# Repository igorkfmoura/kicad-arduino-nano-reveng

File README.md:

# Arduino Nano CH340G Reverse Engineering

## Description

Made on KiCad using manual measurements without consulting official schematics for study purposes.

You may find the pdf version of the  in *./extra* folder.

## Other sources of good knowledge

http://actrl.cz/blog/index.php/2016/arduino-nano-ch340-schematics-and-details/

https://www.instructables.com/id/Arduino-Nano-ATmega238PCH340G-v30-PCB-layout/

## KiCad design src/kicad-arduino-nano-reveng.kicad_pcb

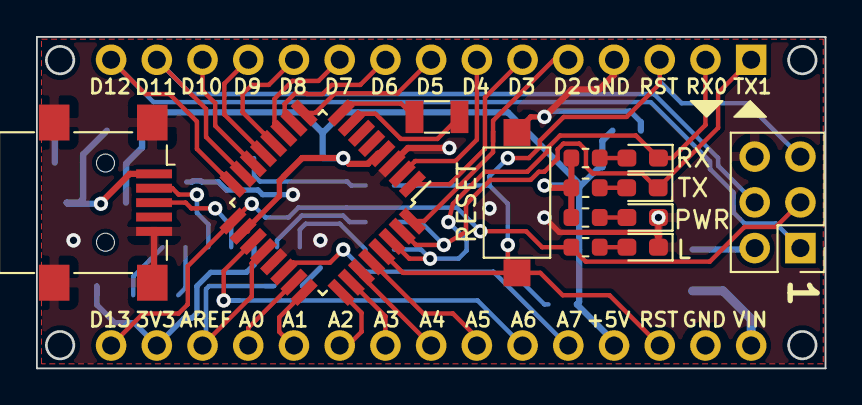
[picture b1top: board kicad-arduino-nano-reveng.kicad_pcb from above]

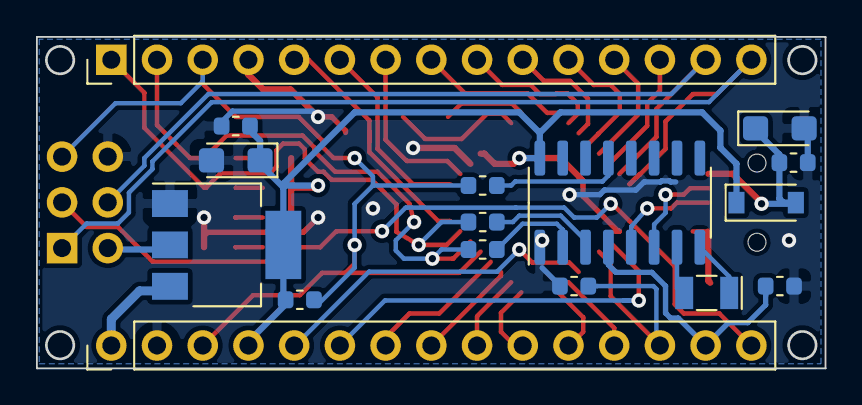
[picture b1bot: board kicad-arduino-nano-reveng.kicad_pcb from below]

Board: 2 copper layers, 43.8 x 18.4 mm, 29 parts (16 on the bottom side), 42 nets.

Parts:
C1, C6: CP; CP_EIA-3216-10_Kemet-I
C2, C3, C4, C5, C7: C; C_0603_1608Metric
D1: RX; LED_0603_1608Metric_Pad1.05x0.95mm_HandSolder
D2: TX; LED_0603_1608Metric_Pad1.05x0.95mm_HandSolder
D3: PWR; LED_0603_1608Metric_Pad1.05x0.95mm_HandSolder
D4: L; LED_0603_1608Metric_Pad1.05x0.95mm_HandSolder
D5: D_Schottky; D_SOD-123
J1: USB_B_Mini; USB_Mini-B_Lumberg_2486_01_Horizontal
J2: ISP; PinHeader_2x03_P2.54mm_Vertical
J3, J4: Conn_01x15; PinHeader_1x15_P2.54mm_Vertical
R1: 103; R_0603_1608Metric
R2, R3: R; R_0603_1608Metric
R4, R5, R6, R7: 102; R_0603_1608Metric
SW1: RESET; SW_SPST_CK_RS282G05A3
U1: AMS1117-5.0; SOT-223-3_TabPin2
U2: ATmega328P-AU; TQFP-32_7x7mm_P0.8mm
U3: CH340G; SOIC-16_3.9x9.9mm_P1.27mm
Y1: Crystal_Atmega; Crystal_SMD_3215-2Pin_3.2x1.5mm
Y2: Crystal; Crystal_SMD_MicroCrystal_CC7V-T1A-2Pin_3.2x1.5mm

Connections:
3V3: C5.2, J4.14, U3.4
+5V: C1.1, C2.1, D5.1, J2.2, J4.4, R1.1, R4.2, R5.2, R6.2, U1.2, U2.4, U2.18, U3.16
A0: J4.12, U2.23
A1: J4.11, U2.24
A2: J4.10, U2.25
A3: J4.9, U2.26
A4: J4.8, U2.27
A5: J4.7, U2.28
A6: J4.6, U2.19
A7: J4.5, U2.22
AREF: C4.2, J4.13, U2.20
D2: J3.5, U2.32
D3: J3.6, U2.1
D4: J3.7, U2.2
D5: J3.8, U2.9
D6: J3.9, U2.10
D7: J3.10, U2.11
D8: J3.11, U2.12
D9: J3.12, U2.13
D10: J3.13, U2.14
D11: J2.4, J3.14, U2.15
D12: J2.1, J3.15, U2.16
D13: J2.3, J4.15, R7.2, U2.17
D+: J1.3, U3.5
D-: J1.2, U3.6
DTR: C3.2, U3.13
GND: C1.2, C2.2, C4.1, C5.1, C6.2, C7.2, D3.1, D4.1, J1.5, J1.6, J2.6, J3.4, J4.2, SW1.2, U1.1, U2.3, U2.21, U3.1
unnamed: D1.2, R4.1
unnamed: D2.2, R5.1
unnamed: D3.2, R6.1
unnamed: D4.2, R7.1
RST: C3.1, J2.5, J3.3, J4.3, R1.2, SW1.1, U2.29
RX0: D1.1, J3.2, R3.2, U2.30
RXD: R2.1, U3.3
TX1: D2.1, J3.1, R2.2, U2.31
TXD: R3.1, U3.2
VIN: J4.1, U1.3
VUSB: C6.1, C7.1, D5.2, J1.1
XI: U3.7, Y2.2
XO: U3.8, Y2.1
XTAL1: U2.7, Y1.1
XTAL2: U2.8, Y1.2

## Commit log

2020-07-30 Pcb edge cuts and top layer components
2020-07-30 back layer components
2020-07-30 Sch front side components
2020-07-30 Wiring
2020-07-31 Almost finishing routing
2020-07-31 Finished wiring
2020-08-01 PCB Rev0
2020-08-01 Rev 0
